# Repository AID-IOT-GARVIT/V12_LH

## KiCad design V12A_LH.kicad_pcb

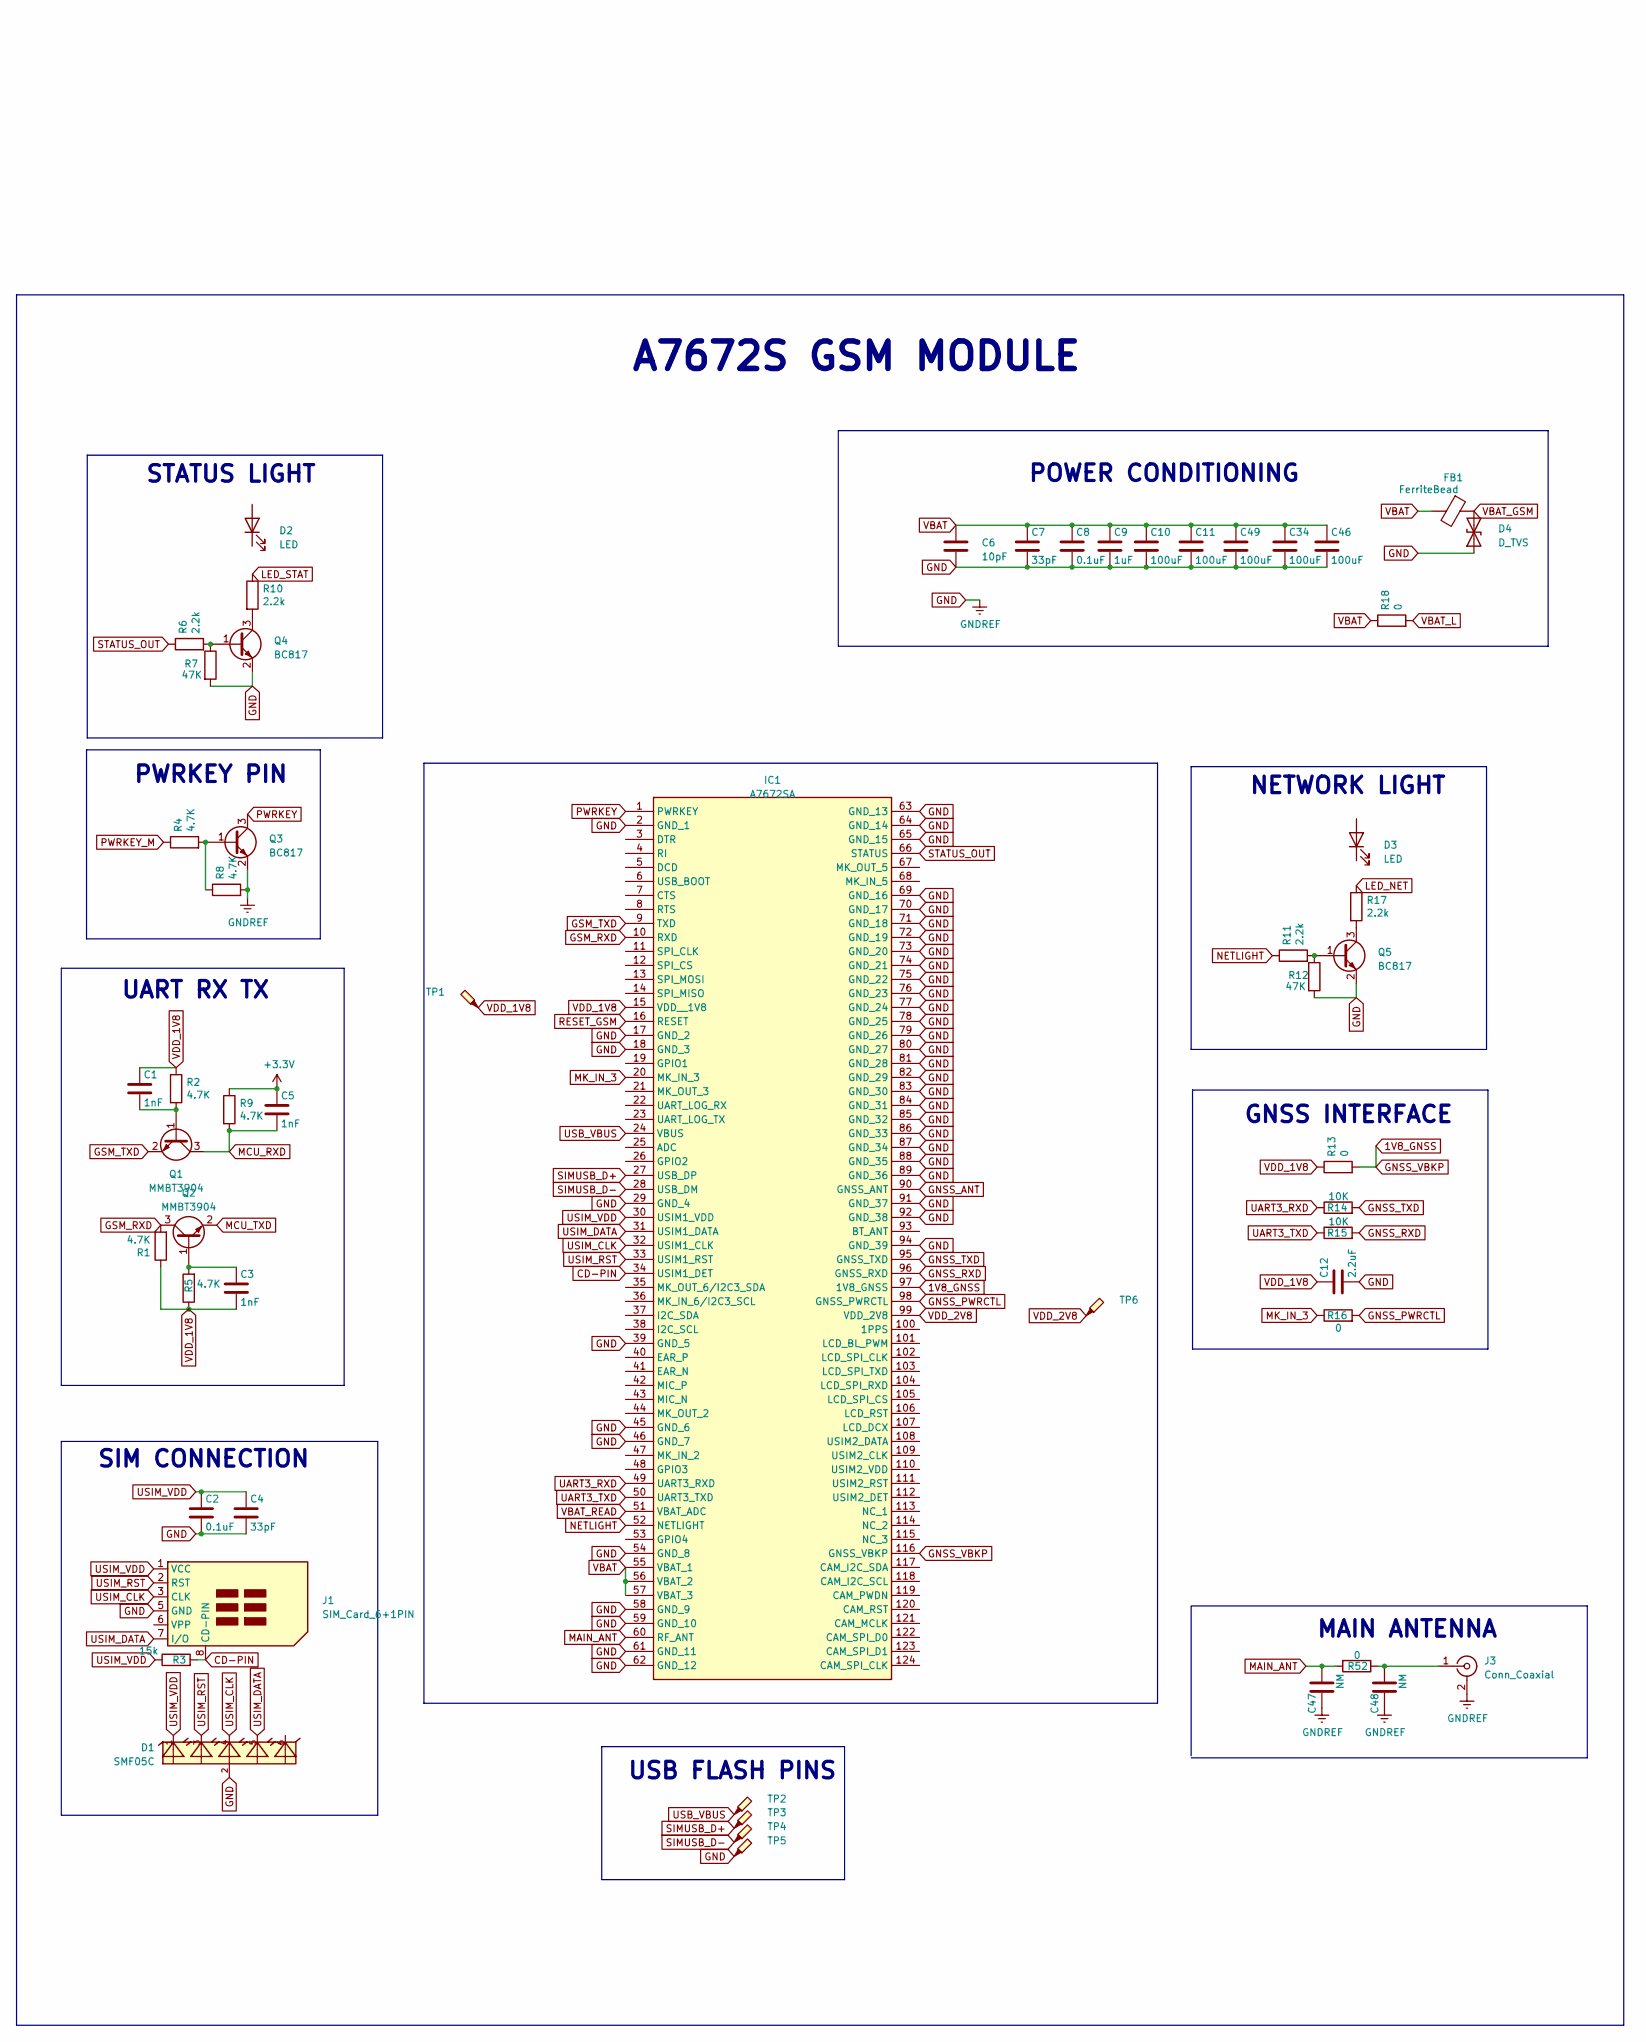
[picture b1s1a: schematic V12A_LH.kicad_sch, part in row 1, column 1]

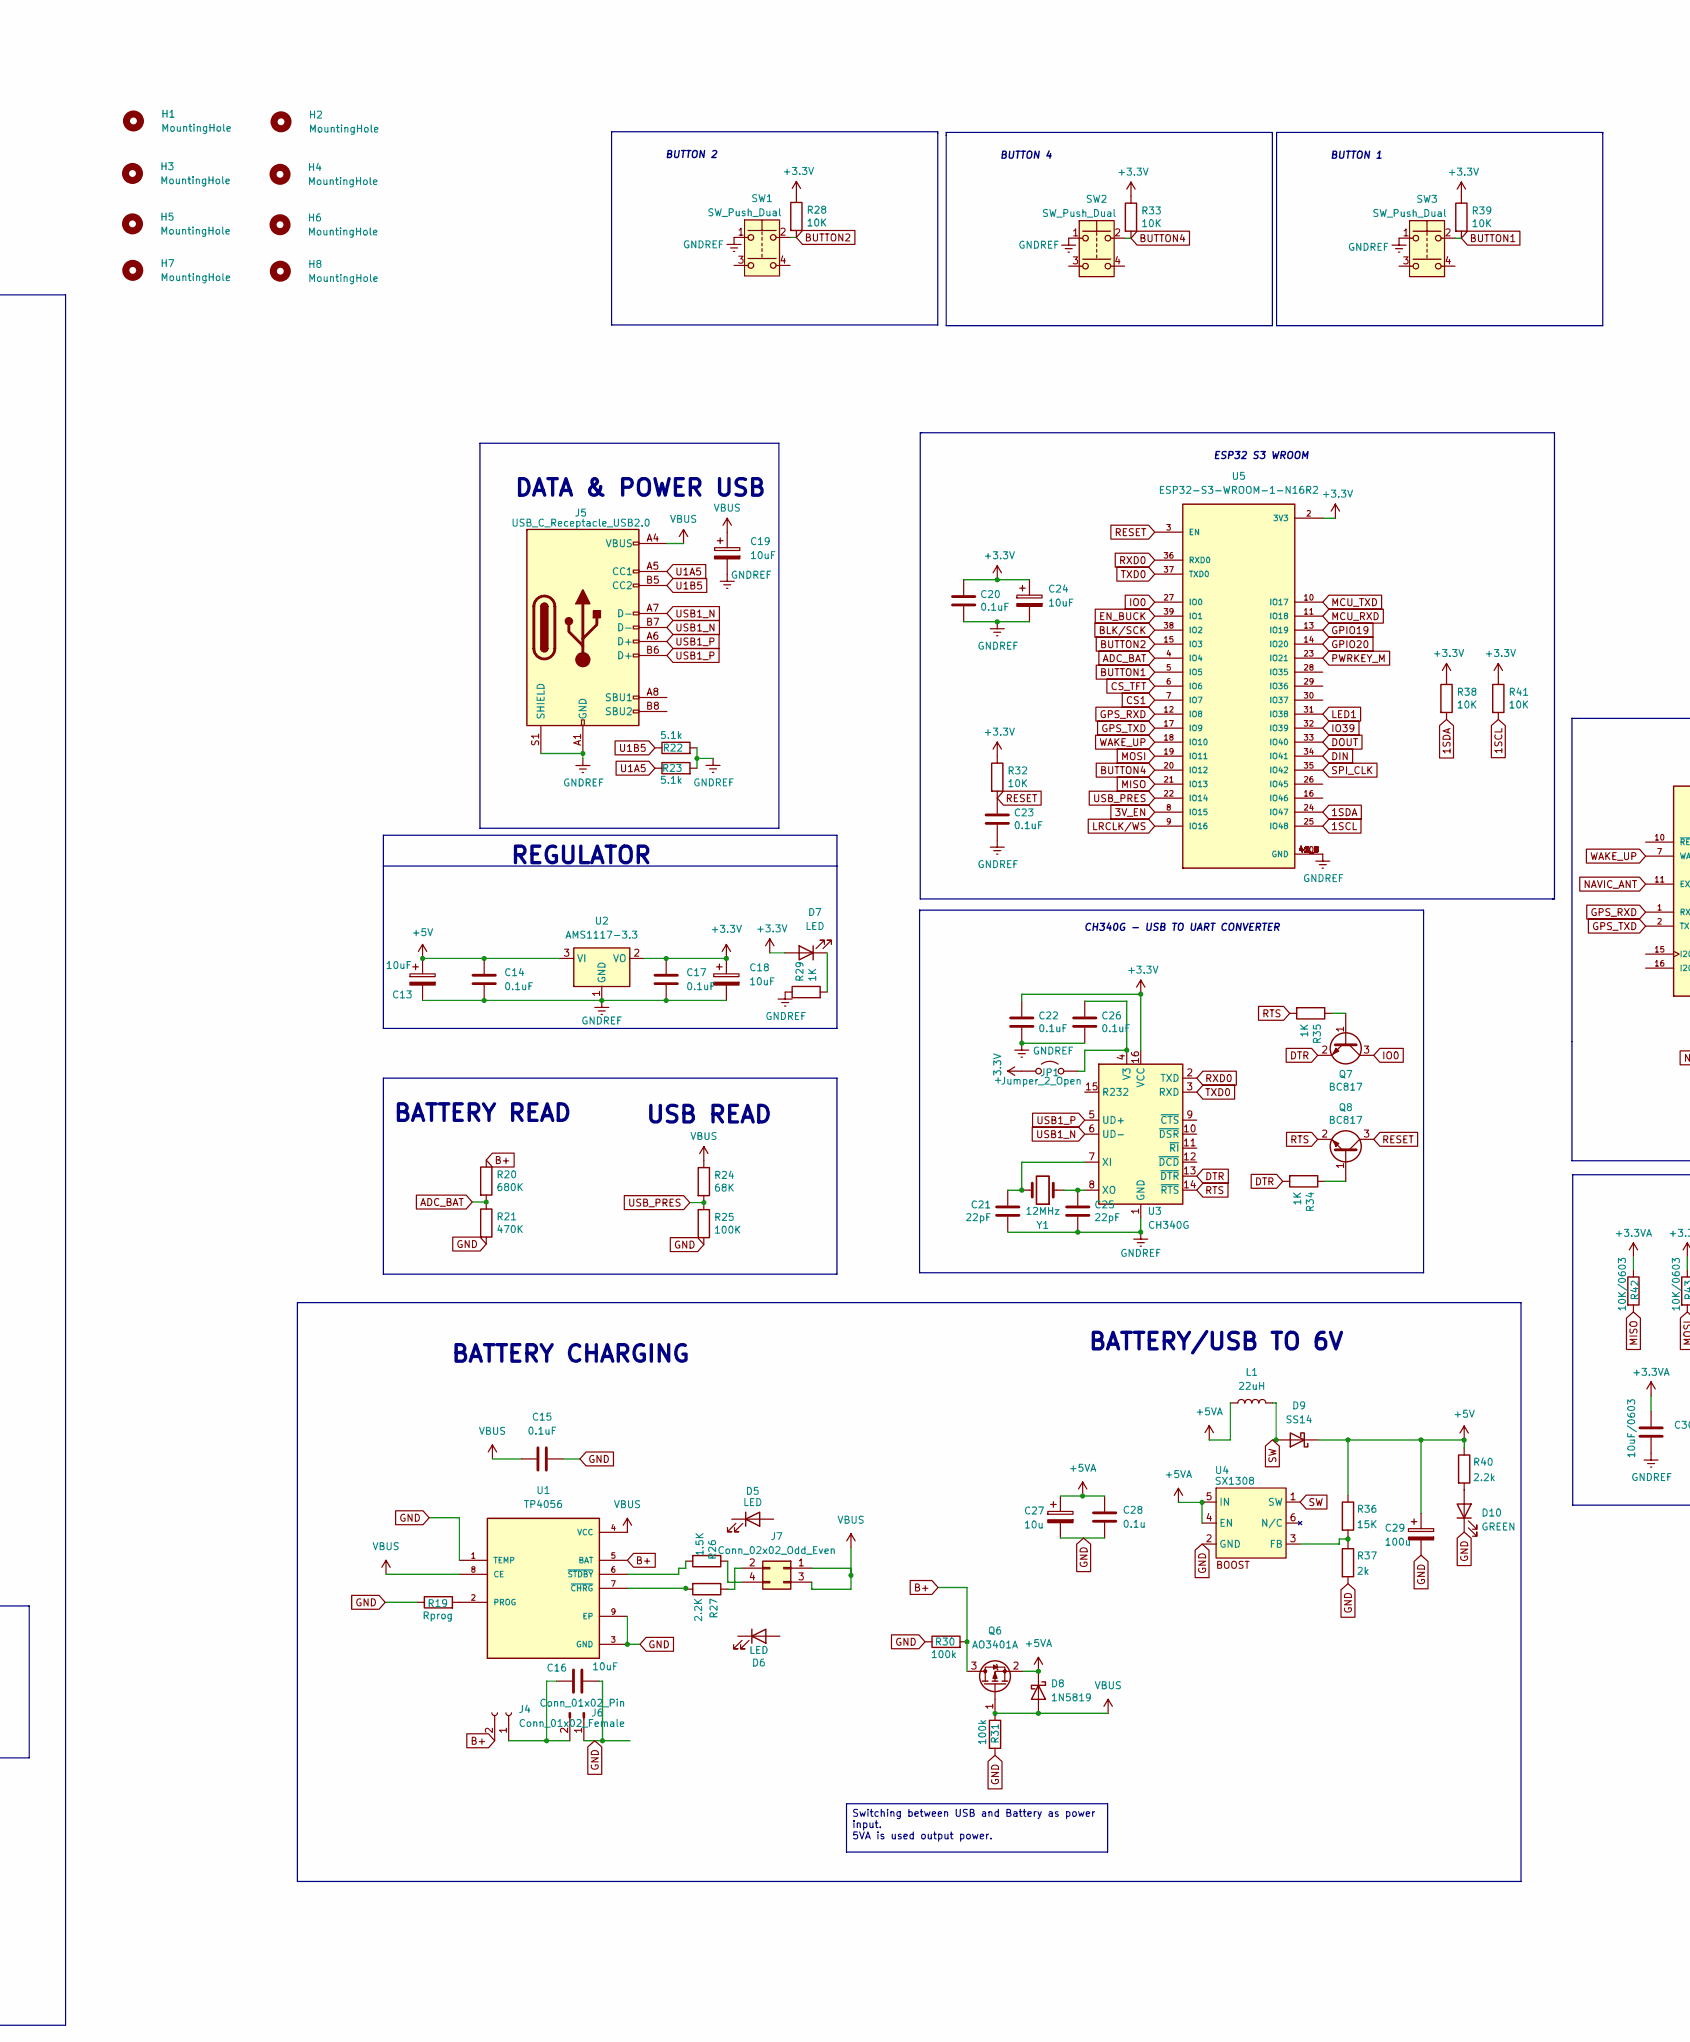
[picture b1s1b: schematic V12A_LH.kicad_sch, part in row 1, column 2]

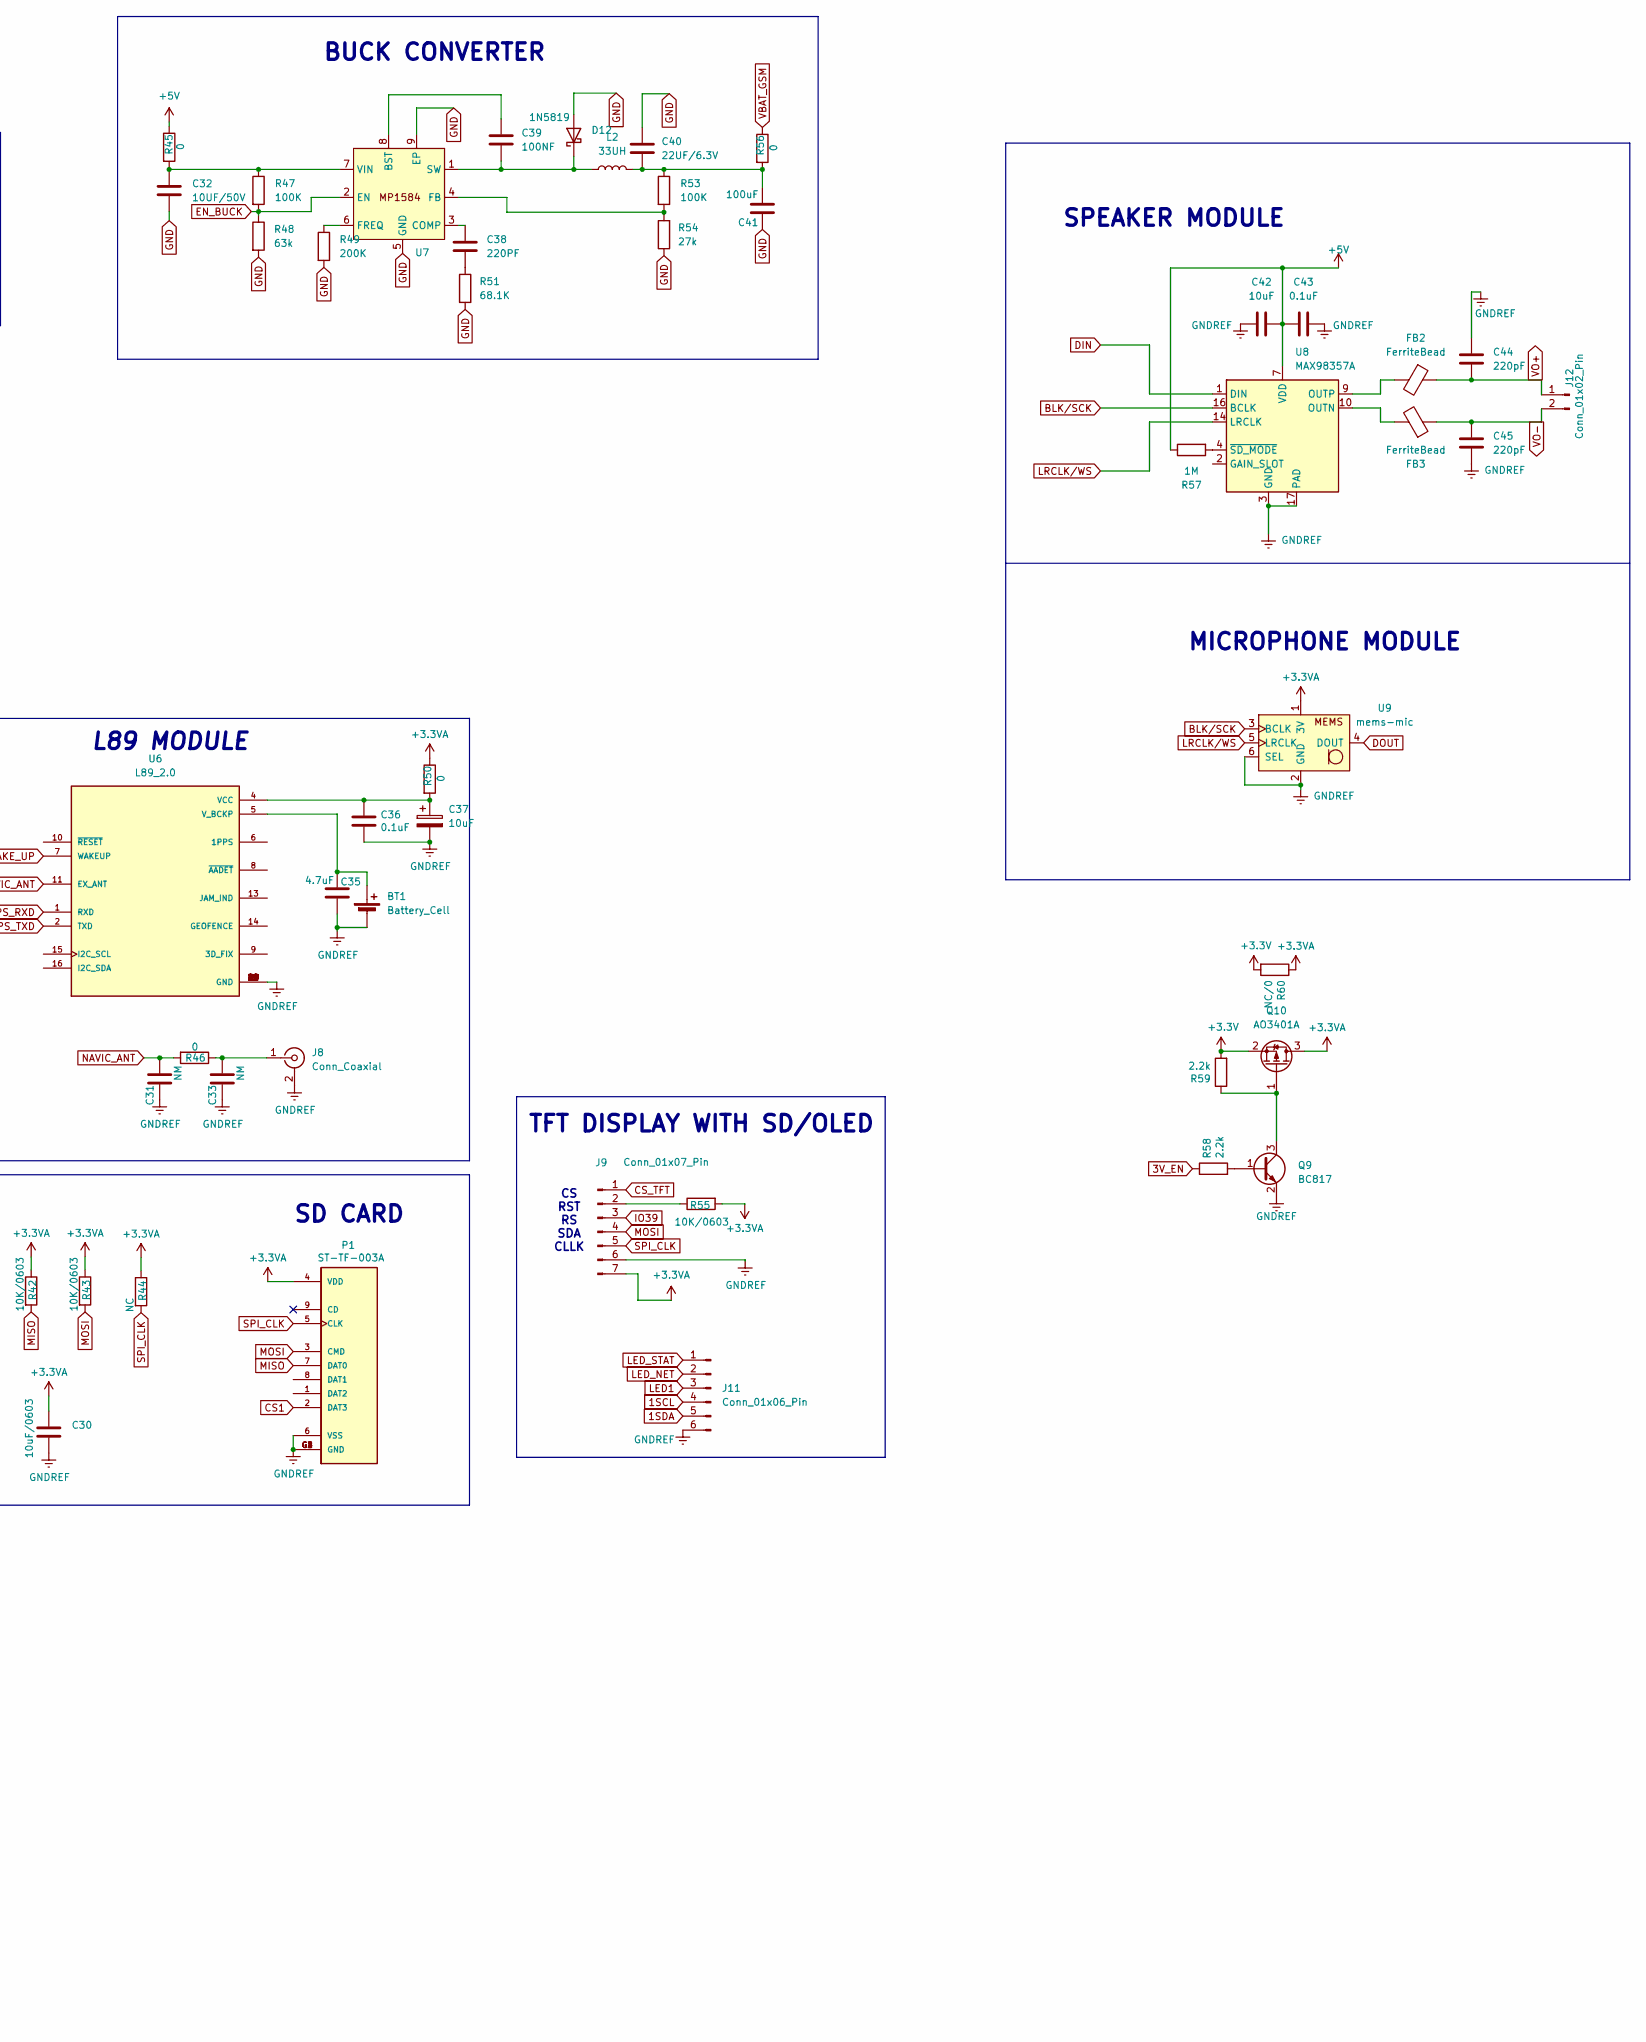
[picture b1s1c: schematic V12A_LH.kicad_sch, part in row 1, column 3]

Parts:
BT1: Battery_Cell; CR1220
C1, C3, C5: 1nF; C_0603_1608Metric
C2, C8, C14, C15, C17, C20, C22, C23, C26: 0.1uF; C_0603_1608Metric
C4, C7: 33pF; C_0603_1608Metric
C6: 10pF; C_0603_1608Metric
C9: 1uF; C_0603_1608Metric
C10, C11, C41, C49: 100uF; C_1206_3216Metric
C12: 2.2uF; C_0805_2012Metric
C13, C18, C19, C24, C37: 10uF; C_1206_3216Metric_Pad1.33x1.80mm_HandSolder
C16: 10uF; C_0805_2012Metric_Pad1.18x1.45mm_HandSolder
C21, C25: 22pF; C_0805_2012Metric
C27: 10u; C_1206_3216Metric
C28: 0.1u; C_0805_2012Metric
C29: 100u; C_1206_3216Metric
C30: 10uF/0603; R_0603_1608Metric
C31, C33, C47, C48: NM; C_0603_1608Metric
C32: 10UF/50V; C_1206_3216Metric
C34, C46: 100uF; CP_Elec_10x10.5
C35: 4.7uF; C_0805_2012Metric
C36, C43: 0.1uF; C_0805_2012Metric
C38: 220PF; C_0805_2012Metric
C39: 100NF; C_0805_2012Metric
C40: 22UF/6.3V; C_1206_3216Metric
C42: 10uF; C_0805_2012Metric
C44, C45: 220pF; C_0805_2012Metric
D1: SMF05C; SC70-6
D2, D3, D5, D6, D7: LED; LED_0805_2012Metric
D4: D_TVS; D_SMB
D8, D12: 1N5819; D_SMA
D9: SS14; D_SMA
D10: GREEN; LED_0805_2012Metric
FB1: FerriteBead; L_1206_3216Metric_Pad1.22x1.90mm_HandSolder
FB2, FB3: FerriteBead; L_0805_2012Metric
H1, H2, H3, H4, H5, H6, H7, H8: MountingHole; MountingHole_2.1mm
IC1: A7672SA; Manufacturer_Part_Number A7672SA
J1: SIM_Card_6+1PIN; Nano_Sim_Holder
J3, J8: Conn_Coaxial; SMA_Samtec_SMA-J-P-X-ST-EM1_EdgeMount
J4: Conn_01x02_Female; PinHeader_1x02_P2.00mm_Vertical
J5: USB_C_Receptacle_USB2.0; USB_C_Receptacle_HRO_TYPE-C-31-M-12
J6, J12: Conn_01x02_Pin; JST_XH_S2B-XH-A_1x02_P2.50mm_Horizontal
J7: Conn_02x02_Odd_Even; PinHeader_2x02_P2.54mm_Vertical
J9: Conn_01x07_Pin; PinHeader_1x07_P2.54mm_Vertical
J11: Conn_01x06_Pin; PinHeader_1x06_P2.54mm_Vertical
JP1: Jumper_2_Open; SolderJumper-2_P1.3mm_Open_RoundedPad1.0x1.5mm
L1: 22uH; L_Cenker_CKCS6045
L2: 33UH; L_7.3x7.3_H3.5
P1: ST-TF-003A; SUNTECH_ST-TF-003A
Q1, Q2: MMBT3904; SOT-23
Q3, Q4, Q5, Q7, Q8, Q9: BC817; SOT-23
Q6, Q10: AO3401A; SOT-23
R1, R2, R4, R5, R8, R9: 4.7K; R_0603_1608Metric
R3: 15k; R_0603_1608Metric
R6, R10, R11, R17, R58, R59: 2.2k; R_0603_1608Metric
R7, R12: 47K; R_0603_1608Metric
R13, R16, R18, R45, R46, R50, R52, R56: 0; R_0603_1608Metric
R14, R15, R28, R32, R33, R38, R39, R41: 10K; R_0603_1608Metric
R19: Rprog; R_0805_2012Metric_Pad1.20x1.40mm_HandSolder
R20: 680K; R_0603_1608Metric
R21: 470K; R_0603_1608Metric
R22, R23: 5.1k; R_0603_1608Metric
R24: 68K; R_0603_1608Metric
R25: 100K; R_0603_1608Metric
R26: 1.5K; R_0603_1608Metric_Pad0.98x0.95mm_HandSolder
R27: 2.2K; R_0603_1608Metric_Pad0.98x0.95mm_HandSolder
R29, R34, R35: 1K; R_0603_1608Metric
R30, R31: 100k; R_0805_2012Metric_Pad1.20x1.40mm_HandSolder
R36: 15K; R_0603_1608Metric_Pad0.98x0.95mm_HandSolder
R37: 2k; R_0805_2012Metric_Pad1.20x1.40mm_HandSolder
R40: 2.2k; R_0603_1608Metric_Pad0.98x0.95mm_HandSolder
R42, R43, R55: 10K/0603; R_0603_1608Metric_Pad0.98x0.95mm_HandSolder
R44: NC; R_0603_1608Metric_Pad0.98x0.95mm_HandSolder
R47, R53: 100K; R_0805_2012Metric
R48: 63k; R_0805_2012Metric
R49: 200K; R_0805_2012Metric
R51: 68.1K; R_0805_2012Metric
R54: 27k; R_0805_2012Metric
R57: 1M; R_0805_2012Metric_Pad1.20x1.40mm_HandSolder
R60: NC/0; R_0603_1608Metric
SW1, SW2, SW3: SW_Push_Dual; SW_Push_4pin_40xx
TP1, TP2, TP3, TP4, TP5, TP6: TestPoint_Probe; TestPoint_Pad_1.0x1.0mm
U1: TP4056; SOIC-8-1EP_3.9x4.9mm_P1.27mm_EP2.514x3.2mm_ThermalVias
U2: AMS1117-3.3; SOT-223-3_TabPin2
U3: CH340G; SOIC-16_3.9x9.9mm_P1.27mm
U4: SX1308; SOT-23-6
U5: ESP32-S3-WROOM-1-N16R2; XCVR_ESP32-S3-WROOM-1-N16R2; PARTREV v1.0
U6: L89_2.0; XCVR_L89_2.0; PARTREV 1.2
U7: SOIC-8-1EP_3.9x4.9mm_P1.27mm_EP2.29x3mm_ThermalVias
U8: MAX98357A; TQFN-16-1EP_3x3mm_P0.5mm_EP1.23x1.23mm
U9: mems-mic; mems-mic-round
Y1: 12MHz; Crystal_SMD_HC49-SD

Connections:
1SCL: J11.4, R41.2, U5.25 (IO48)
1SDA: J11.5, R38.2, U5.24 (IO47)
1V8_GNSS: IC1.97 (1V8_GNSS), IC1.116 (GNSS_VBKP), R13.2
3V_EN: R58.1, U5.8 (IO15)
+3.3V: C5.1, C17.1, C18.1, C20.1, C22.1, C24.1, D7.2 (A), JP1.1 (A), Q10.2 (S), R9.1, R28.1, R32.1, R33.1, R38.1, R39.1, R41.1, R59.2, R60.2, U2.2 (VO), U3.16 (VCC), U5.2 (3V3)
+3.3VA: C30.1, J9.7, P1.4 (VDD), Q10.3 (D), R42.1, R43.1, R44.1, R50.1, R55.2, R60.1, U9.1 (3V)
+5V: C13.1, C14.1, C29.1, C42.2, C43.1, D9.1 (K), R36.1, R40.1, R45.1, R57.1, U2.3 (VI), U8.7 (VDD), U8.8 (VDD)
+5VA: C27.1, C28.1, D8.1 (K), L1.1, Q6.2 (S), U4.4 (EN), U4.5 (IN)
ADC_BAT: R20.2, R21.1, U5.4 (IO4)
B+: J4.2, Q6.3 (D), R20.1, R30.2, U1.5 (BAT)
BLK/SCK: U5.38 (IO2), U8.16 (BCLK), U9.3 (BCLK)
BUTTON1: R39.2, SW3.2, U5.5 (IO5)
BUTTON2: R28.2, SW1.2, U5.15 (IO3)
BUTTON4: R33.2, SW2.2, U5.20 (IO12)
CD-PIN: IC1.34 (USIM1_DET), J1.8 (CD-PIN), R3.2
CS1: P1.2 (DAT3), U5.7 (IO7)
CS_TFT: J9.1, U5.6 (IO6)
DIN: U5.34 (IO41), U8.1 (DIN)
DOUT: U5.33 (IO40), U9.4 (DOUT)
DTR: Q7.2 (E), R34.2, U3.13 (~DTR)
EN_BUCK: R47.2, R48.1, U5.39 (IO1), U7.2 (EN)
GND: BT1.2 (-), C2.2, C4.2, C6.2, C7.2, C8.2, C9.2, C10.2, C11.2, C12.2, C13.2, C14.2, C15.2, C16.2, C17.2, C18.2, C19.2, C20.2, C21.1, C22.2, C23.2, C24.2, C25.2, C26.1, C27.2, C28.2, C29.2, C30.2, C31.1, C32.2, C33.1, C34.2, C35.2, C36.2, C37.2, C40.2, C41.1, C42.1, C43.2, C44.1, C45.1, C46.2, C47.1, C48.1, C49.2, D1.2, D4.1 (A1), D10.1 (K), D12.2 (A), IC1.2 (GND_1), IC1.17 (GND_2), IC1.18 (GND_3), IC1.29 (GND_4), IC1.39 (GND_5), IC1.45 (GND_6), IC1.46 (GND_7), IC1.54 (GND_8), IC1.58 (GND_9), IC1.59 (GND_10), IC1.61 (GND_11), IC1.62 (GND_12), IC1.63 (GND_13), IC1.64 (GND_14), IC1.65 (GND_15), IC1.69 (GND_16), IC1.70 (GND_17), IC1.71 (GND_18), IC1.72 (GND_19), IC1.73 (GND_20), IC1.74 (GND_21), IC1.75 (GND_22), IC1.76 (GND_23), IC1.77 (GND_24), IC1.78 (GND_25), IC1.79 (GND_26), IC1.80 (GND_27), IC1.81 (GND_28), IC1.82 (GND_29), IC1.83 (GND_30), IC1.84 (GND_31), IC1.85 (GND_32), IC1.86 (GND_33), IC1.87 (GND_34), IC1.88 (GND_35), IC1.89 (GND_36), IC1.91 (GND_37), IC1.92 (GND_38), IC1.94 (GND_39), J1.5 (GND), J3.2 (Ext), J5.A1 (GND), J5.A12 (GND), J5.B1 (GND), J5.B12 (GND), J5.S1 (SHIELD), J6.1, J8.2 (Ext), J9.6, J11.6, P1.6 (VSS), P1.G1 (GND), P1.G2 (GND), P1.G3 (GND), P1.G4 (GND), Q3.2 (E), Q4.2 (E), Q5.2 (E), Q9.2 (E), R7.2, R8.2, R12.2, R19.1, R21.2, R22.2, R23.2, R25.2, R29.1, R30.1, R31.2, R37.2, R48.2, R49.2, R51.2, R54.1, SW1.1, SW2.1, SW3.1, TP5.1, U1.1 (TEMP), U1.3 (GND), U1.9 (EP), U2.1 (GND), U3.1 (GND), U4.2 (GND), U5.1 (GND), U5.40 (GND), U5.41_1 (GND), U5.41_2 (GND), U5.41_3 (GND), U5.41_4 (GND), U5.41_5 (GND), U5.41_6 (GND), U5.41_7 (GND), U5.41_8 (GND), U5.41_9 (GND), U6.3 (GND), U6.12 (GND), U6.17 (GND), U6.18 (GND), U6.19 (GND), U6.20 (GND), U6.21 (GND), U6.22 (GND), U6.23 (GND), U6.24 (GND), U6.25 (GND), U6.26 (GND), U6.27 (GND), U6.28 (GND), U6.29 (GND), U6.30 (GND), U6.31 (GND), U6.32 (GND), U6.33 (GND), U6.34 (GND), U6.35 (GND), U6.36 (GND), U6.37 (GND), U6.38 (GND), U6.39 (GND), U6.40 (GND), U6.41 (GND), U6.42 (GND), U6.43 (GND), U6.44 (GND), U6.45 (GND), U7.5 (GND), U7.9 (EP), U8.3 (GND), U8.11 (GND), U8.15 (GND), U8.17 (PAD), U9.2 (GND), U9.6 (SEL)
GNSS_ANT: IC1.90 (GNSS_ANT)
GNSS_PWRCTL: IC1.98 (GNSS_PWRCTL), R16.2
GNSS_RXD: IC1.96 (GNSS_RXD), R15.2
GNSS_TXD: IC1.95 (GNSS_TXD), R14.2
GPIO19: U5.13 (IO19)
GPIO20: U5.14 (IO20)
GPS_RXD: U5.12 (IO8), U6.1 (RXD)
GPS_TXD: U5.17 (IO9), U6.2 (TXD)
GSM_RXD: IC1.10 (RXD), Q2.3 (C), R1.2
GSM_TXD: IC1.9 (TXD), Q1.2 (E)
IO0: Q7.3 (C), U5.27 (IO0)
IO39: J9.3, U5.32 (IO39)
LED1: J11.3, U5.31 (IO38)
LED_NET: J11.2, R17.1
LED_STAT: J11.1, R10.1
LRCLK/WS: U5.9 (IO16), U8.14 (LRCLK), U9.5 (LRCLK)
MAIN_ANT: C47.2, IC1.60 (RF_ANT), R52.2
MCU_RXD: C5.2, Q1.3 (C), R9.2, U5.11 (IO18)
MCU_TXD: Q2.2 (E), U5.10 (IO17)
MISO: P1.7 (DAT0), R42.2, U5.21 (IO13)
MK_IN_3: IC1.20 (MK_IN_3), R16.1
MOSI: J9.4, P1.3 (CMD), R43.2, U5.19 (IO11)
NAVIC_ANT: C31.2, R46.2, U6.11 (EX_ANT)
NETLIGHT: IC1.52 (NETLIGHT), R11.1
unnamed: BT1.1 (+), C35.1, U6.5 (V_BCKP)
unnamed: C38.2, R51.1
unnamed: C40.1, C41.2, L2.2, R53.1, R56.2
unnamed: D7.1 (K), R29.2
unnamed: D10.2 (A), R40.2
unnamed: C39.2, D12.1 (K), L2.1, U7.1 (SW)
unnamed: C48.2, J3.1 (In), R52.1
unnamed: C16.1, J4.1, J6.2
unnamed: J7.2, R27.1
unnamed: J7.4, R26.1
unnamed: C33.2, J8.1 (In), R46.1
unnamed: J9.2, R55.1
unnamed: C26.2, JP1.2 (B), U3.4 (V3)
unnamed: C1.2, Q1.1 (B), R2.2
unnamed: C3.1, Q2.1 (B), R5.2
unnamed: Q3.1 (B), R4.2, R8.1
unnamed: Q4.1 (B), R6.2, R7.1
unnamed: Q4.3 (C), R10.2
unnamed: Q5.1 (B), R11.2, R12.1
unnamed: Q5.3 (C), R17.2
unnamed: Q7.1 (B), R35.1
unnamed: Q8.1 (B), R34.1
unnamed: Q9.1 (B), R58.2
unnamed: Q9.3 (C), Q10.1 (G), R59.1
unnamed: R19.2, U1.2 (PROG)
unnamed: R27.2, U1.7 (~CHRG)
unnamed: R26.2, U1.6 (~STDBY)
unnamed: C21.2, U3.7 (XI), Y1.2
unnamed: C25.1, U3.8 (XO), Y1.1
unnamed: R36.2, R37.1, U4.3 (FB)
unnamed: C36.1, C37.1, R50.2, U6.4 (VCC)
unnamed: C39.1, U7.8 (BST)
unnamed: C38.1, U7.3 (COMP)
unnamed: R53.2, R54.2, U7.4 (FB)
unnamed: R49.1, U7.6 (FREQ)
unnamed: C32.1, R45.2, R47.1, U7.7 (VIN)
unnamed: FB3.2, U8.10 (OUTN)
unnamed: FB2.2, U8.9 (OUTP)
unnamed: R57.2, U8.4 (~SD_MODE)
PWRKEY: IC1.1 (PWRKEY), Q3.3 (C)
PWRKEY_M: R4.1, U5.23 (IO21)
RESET: C23.1, Q8.3 (C), R32.2, U5.3 (EN)
RESET_GSM: IC1.16 (RESET)
RTS: Q8.2 (E), R35.2, U3.14 (~RTS)
RXD0: U3.2 (TXD), U5.36 (RXD0)
SIMUSB_D+: IC1.27 (USB_DP), TP3.1
SIMUSB_D-: IC1.28 (USB_DM), TP4.1
SPI_CLK: J9.5, P1.5 (CLK), R44.2, U5.35 (IO42)
STATUS_OUT: IC1.66 (STATUS), R6.1
SW: D9.2 (A), L1.2, U4.1 (SW)
TXD0: U3.3 (RXD), U5.37 (TXD0)
U1A5: J5.A5 (CC1), R23.1
U1B5: J5.B5 (CC2), R22.1
UART3_RXD: IC1.49 (UART3_RXD), R14.1
UART3_TXD: IC1.50 (UART3_TXD), R15.1
USB1_N: J5.A7 (D-), J5.B7 (D-), U3.6 (UD-)
USB1_P: J5.A6 (D+), J5.B6 (D+), U3.5 (UD+)
USB_PRES: R24.2, R25.1, U5.22 (IO14)
USB_VBUS: IC1.24 (VBUS), TP2.1
USIM_CLK: D1.4, IC1.32 (USIM1_CLK), J1.3 (CLK)
USIM_DATA: D1.5, IC1.31 (USIM1_DATA), J1.7 (I/O)
USIM_RST: D1.3, IC1.33 (USIM1_RST), J1.2 (RST)
USIM_VDD: C2.1, C4.1, D1.1, IC1.30 (USIM1_VDD), J1.1 (VCC), R3.1
VBAT: C6.1, C7.1, C8.1, C9.1, C10.1, C11.1, C34.1, C46.1, C49.1, FB1.2, IC1.55 (VBAT_1), IC1.56 (VBAT_2), IC1.57 (VBAT_3), R18.1
VBAT_GSM: D4.2 (A2), FB1.1, R56.1
VBAT_L: R18.2
VBAT_READ: IC1.51 (VBAT_ADC)
VBUS: C15.1, C19.1, D8.2 (A), J5.A4 (VBUS), J5.A9 (VBUS), J5.B4 (VBUS), J5.B9 (VBUS), J7.1, J7.3, Q6.1 (G), R24.1, R31.1, U1.4 (VCC), U1.8 (CE)
VDD_1V8: C1.1, C3.2, C12.1, IC1.15 (VDD__1V8), R1.1, R2.1, R5.1, R13.1, TP1.1
VDD_2V8: IC1.99 (VDD_2V8), TP6.1
VO+: C44.2, FB2.1, J12.1
VO-: C45.2, FB3.1, J12.2
WAKE_UP: U5.18 (IO10), U6.7 (WAKEUP)

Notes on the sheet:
BUCK CONVERTER
A7672S GSM MODULE
SPEAKER MODULE
BUTTON 4
NETWORK LIGHT
BUTTON 2
CS RST RS SDA CLLK
UART RX TX
GNSS INTERFACE
BUTTON 1
USB FLASH PINS
SIM CONNECTION
BATTERY READ
CH340G - USB TO UART CONVERTER
STATUS LIGHT
TFT DISPLAY WITH SD/OLED
USB READ
REGULATOR
MICROPHONE MODULE
PWRKEY PIN
POWER CONDITIONING
DATA & POWER USB
MAIN ANTENNA
ESP32 S3 WROOM
BATTERY/USB TO 6V
L89 MODULE
SD CARD
BATTERY CHARGING
Switching between USB and Battery as power input. 5VA is used output power.

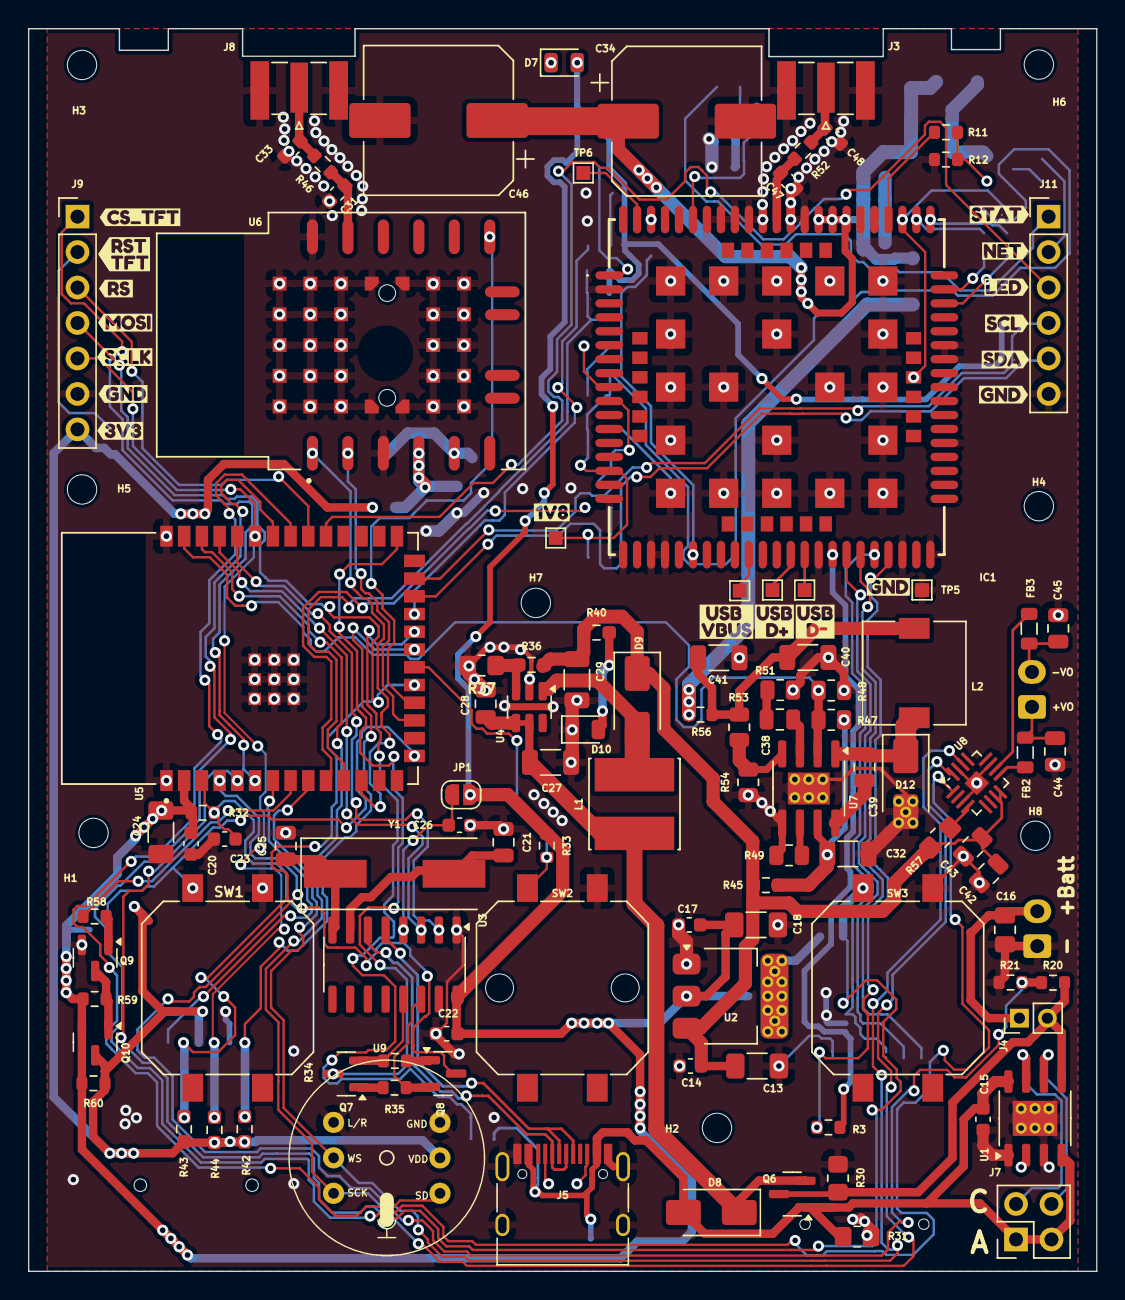
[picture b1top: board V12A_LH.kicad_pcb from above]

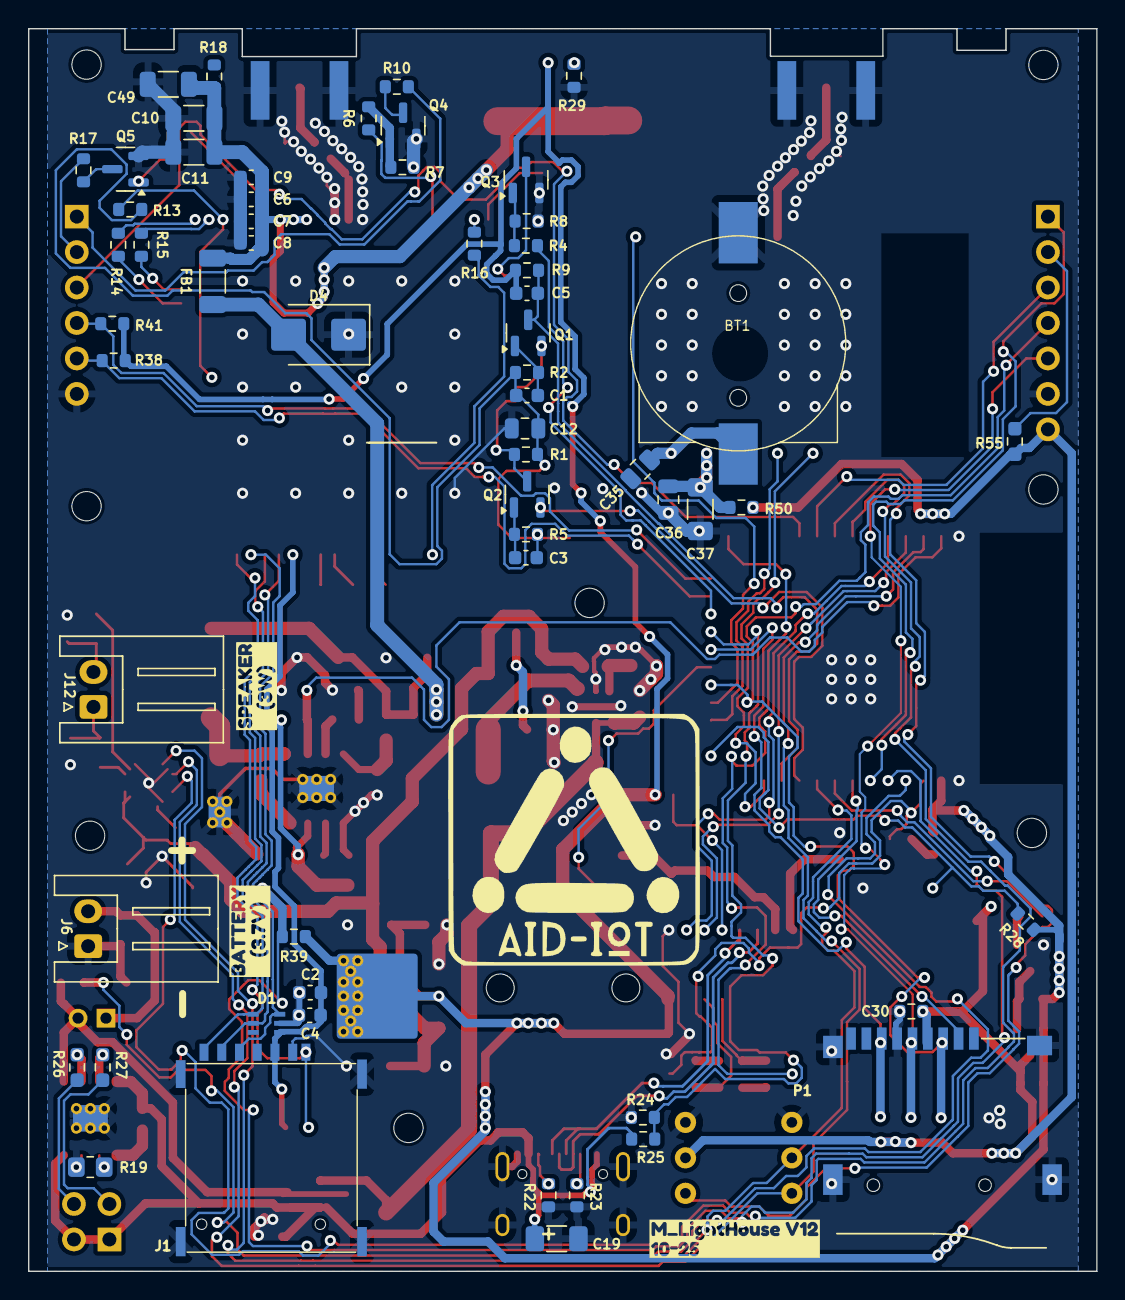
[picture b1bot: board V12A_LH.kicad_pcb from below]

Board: 2 copper layers, 76.5 x 89.0 mm, 193 parts (63 on the bottom side), 113 nets.

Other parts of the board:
kibuzzard-68EA22D5: G***; kibuzzard-68EA22D5
kibuzzard-68EA253F: G***; kibuzzard-68EA253F
kibuzzard-68EA2556: G***; kibuzzard-68EA2556
kibuzzard-68EBC577: G***; kibuzzard-68EBC577
kibuzzard-6867B3A9: G***; kibuzzard-6867B3A9
kibuzzard-6867B3BB: G***; kibuzzard-6867B3BB
kibuzzard-6867B4CE: G***; kibuzzard-6867B4CE
kibuzzard-6867B4EC: G***; kibuzzard-6867B4EC
kibuzzard-6867B4F7: G***; kibuzzard-6867B4F7
kibuzzard-6867B33D: G***; kibuzzard-6867B33D
kibuzzard-6867B38E: G***; kibuzzard-6867B38E
kibuzzard-6867B39F: G***; kibuzzard-6867B39F
kibuzzard-6867B375: G***; kibuzzard-6867B375
kibuzzard-6867B426: G***; kibuzzard-6867B426
kibuzzard-6867B475: G***; kibuzzard-6867B475
kibuzzard-6867B505: G***; kibuzzard-6867B505
kibuzzard-6868C5A9: G***; kibuzzard-6868C5A9
kibuzzard-6868C5C3: G***; kibuzzard-6868C5C3
kibuzzard-6868C5F0: G***; kibuzzard-6868C5F0
kibuzzard-6868C531: G***; kibuzzard-6868C531
kibuzzard-6868C585: G***; kibuzzard-6868C585

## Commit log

2025-12-02 version 12
